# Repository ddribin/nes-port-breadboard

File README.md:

# NES Port Breadboard Adapter

A breadboard adapter for a console-side (male) NES port, specifically the [Raphnet right-angle NES controller connector][1].

Top of PCB:

Bottom of PCB:

[1]: https://www.raphnet-tech.com/products/nes_controller_connector/index.php

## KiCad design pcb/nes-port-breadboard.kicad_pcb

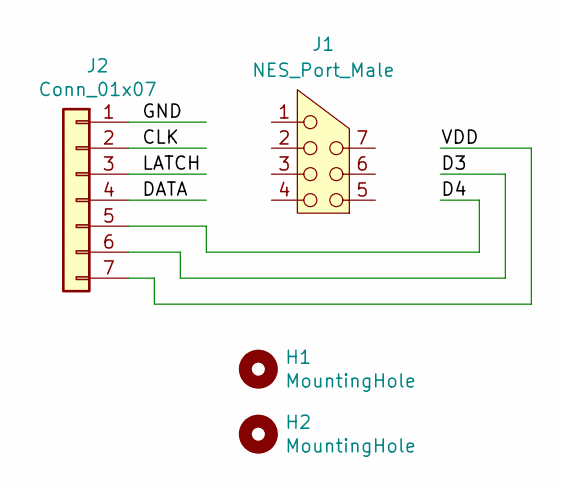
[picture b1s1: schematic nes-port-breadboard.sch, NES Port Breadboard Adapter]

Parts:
H1, H2: MountingHole; MountingHole_2.7mm_M2.5
J1: NES_Port_Male; NES_Port_Male_Horizontal
J2: Conn_01x07; PinHeader_1x07_P2.54mm_Vertical

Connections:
/CLK: J1.2, J2.2
/D3: J1.6, J2.6
/D4: J1.5, J2.5
/DATA: J1.4, J2.4
/GND: J1.1, J2.1
/LATCH: J1.3, J2.3
/VDD: J1.7, J2.7

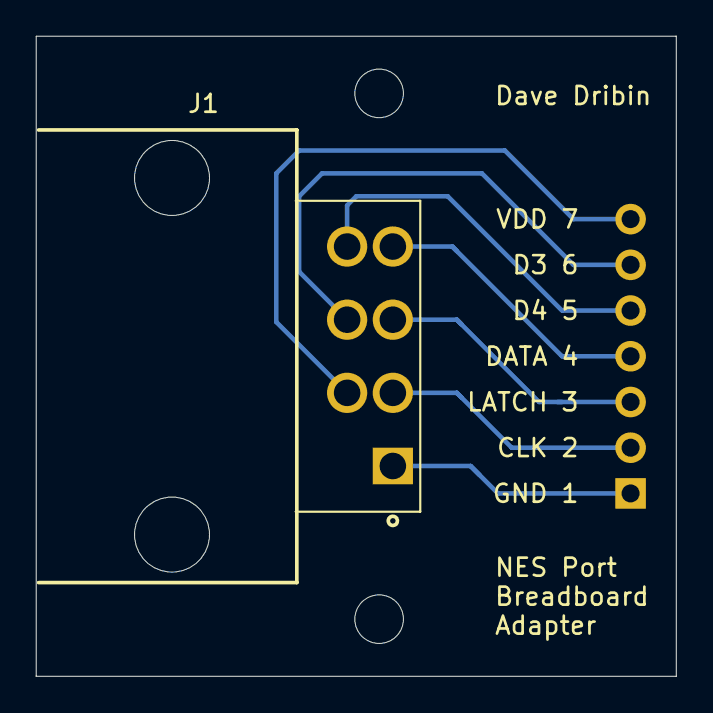
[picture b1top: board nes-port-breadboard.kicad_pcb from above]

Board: 2 copper layers, 35.6 x 35.6 mm, 4 parts (1 on the bottom side), 7 nets.

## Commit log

2021-06-10 Initial import
2021-06-12 Update silkscreen
2021-06-12 Squish board to 1.5x1.5
2021-06-13 Rename nes-breadboard -> nes-port-breadboard
2021-06-13 Add LICENSE and README.md
    Upadate license and version in KiCad docs.
2021-06-14 Update mounting holes
2021-06-14 Update schematic to have a background
2021-06-14 Update dimensions
2021-06-14 Tweak tracks. Update Gerber and drill settings. Add mounting hole labels.
2021-06-15 Add PCB images to README
2021-06-15 Fix link to Raphnet
2021-07-03 Update footprint filter to work for library symbol
2021-07-05 Make NES port holes bigger. Shrink board to 1.4x1.4 inches
2021-07-05 Tweak footprint og NES port
2021-07-05 NES Port footprint: Move pins left 0.010 inch
2021-07-06 Update PCB with new NES port footprint
2021-07-06 Tweak bottom silk. Prep for Gerbers.
2021-07-06 Center NES port vertically
2021-07-07 Update schematic symbol for NES port
2021-07-07 Tweak label positions in schematic
    Add *.pdf to .gitignore
2021-07-08 Fix a stray edge cut
2021-08-02 Update PCB images
2021-08-02 Add CHANGES.md

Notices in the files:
pcb/nes-port-breadboard.kicad_pcb:
MIT License
